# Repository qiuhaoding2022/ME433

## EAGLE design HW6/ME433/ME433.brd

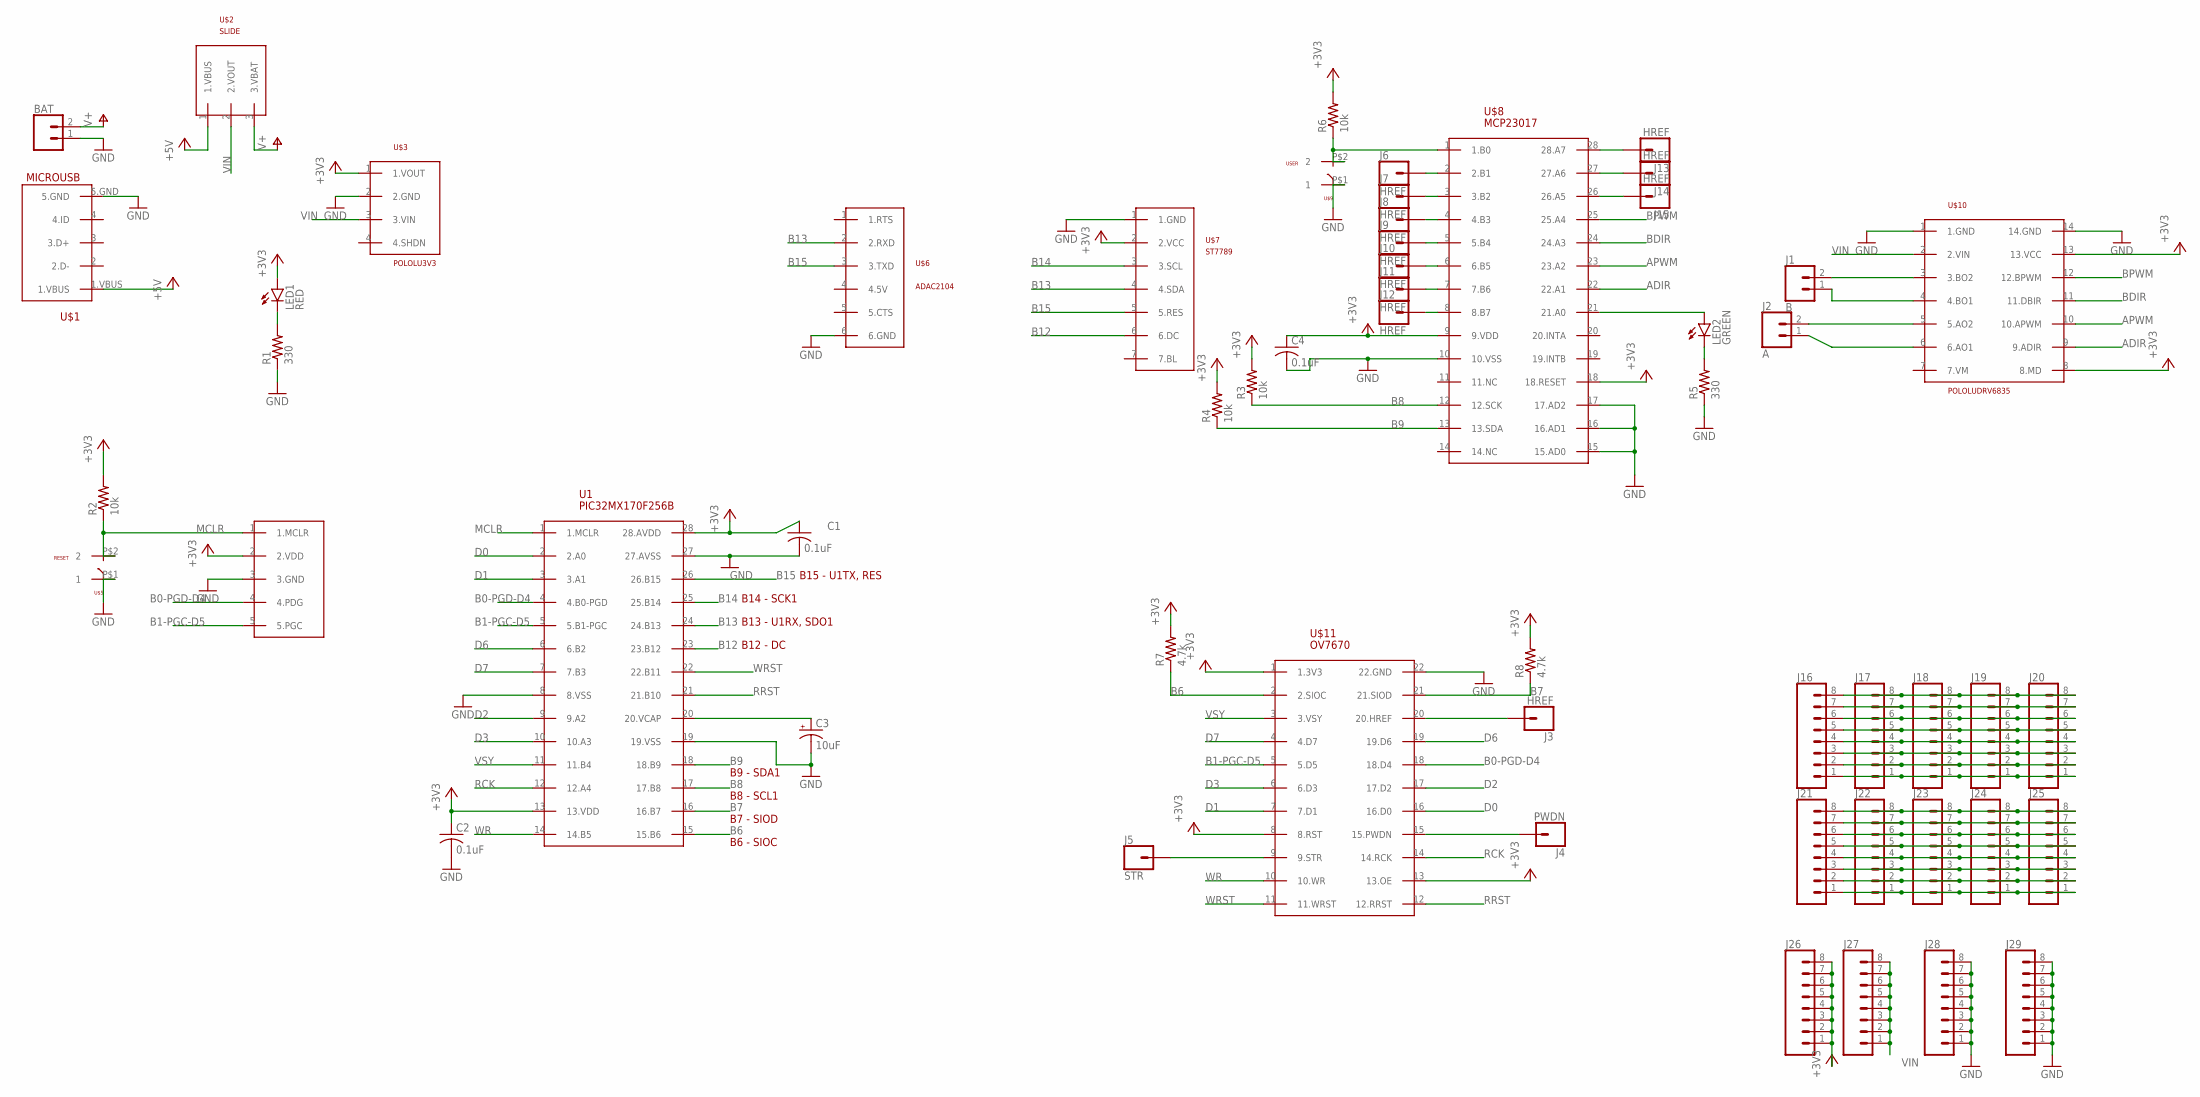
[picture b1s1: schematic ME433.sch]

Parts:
BAT: CONN_02; 1X02
C1, C2, C4: 0.1uF; C025-030X050
C3: 10uF; B45181B
J1: B; 1X02
J2: A; 1X02
J3, J6, J7, J8, J9, J10, J11, J12, J13, J14, J15: HREF; 1X01
J4: PWDN; 1X01
J5: STR; 1X01
J16, J17, J18, J19, J20, J21, J22, J23, J24, J25, J26, J27, J28, J29: CONN_08"; 1X08
LED1: RED; LED3MM
LED2: GREEN; LED3MM
R1, R5: 330; 0207/10
R2, R3, R4, R6: 10k; 0207/10
R7, R8: 4.7k; 0207/10
U1: PIC32MX170F256B; DIL28-3
U$1: MICROUSB
U$2: SLIDE
U$3: POLOLU3V3
U$4: SNAP
U$5: RESET; PUSH
U$6: ADAC2104
U$7: ST7789
U$8: MCP23017; DIL28-3
U$9: USER; PUSH
U$10: POLOLUDRV6835
U$11: OV7670

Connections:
+3V3: C1.1, C2.1, C4.1, J26.1, J26.2, J26.3, J26.4, J26.5, J26.6, J26.7, J26.8, LED1.A, R2.2, R3.2, R4.2, R6.2, R7.2, R8.2, U1.13 (13.VDD), U1.28 (28.AVDD), U$3.1 (1.VOUT), U$4.2 (2.VDD), U$7.2 (2.VCC), U$8.9 (9.VDD), U$8.18 (18.RESET), U$10.8 (8.MD), U$10.13 (13.VCC), U$11.1 (1.3V3), U$11.8 (8.RST), U$11.13 (13.OE)
+5V: U$1.1.VBUS, U$2.1 (1.VBUS)
ADIR: U$8.22 (22.A1), U$10.9 (9.ADIR)
APWM: U$8.23 (23.A2), U$10.10 (10.APWM)
B0-PGD-D4: U1.4 (4.B0-PGD), U$4.4 (4.PDG), U$11.18 (18.D4)
B1-PGC-D5: U1.5 (5.B1-PGC), U$4.5 (5.PGC), U$11.5 (5.D5)
B6: R7.1, U1.15 (15.B6), U$11.2 (2.SIOC)
B7: R8.1, U1.16 (16.B7), U$11.21 (21.SIOD)
B8: R3.1, U1.17 (17.B8), U$8.12 (12.SCK)
B9: R4.1, U1.18 (18.B9), U$8.13 (13.SDA)
B12: U1.23 (23.B12), U$7.6 (6.DC)
B13: U1.24 (24.B13), U$6.2 (2.RXD), U$7.4 (4.SDA)
B14: U1.25 (25.B14), U$7.3 (3.SCL)
B15: U1.26 (26.B15), U$6.3 (3.TXD), U$7.5 (5.RES)
BDIR: U$8.24 (24.A3), U$10.11 (11.DBIR)
BPWM: U$8.25 (25.A4), U$10.12 (12.BPWM)
D0: U1.2 (2.A0), U$11.16 (16.D0)
D1: U1.3 (3.A1), U$11.7 (7.D1)
D2: U1.9 (9.A2), U$11.17 (17.D2)
D3: U1.10 (10.A3), U$11.6 (6.D3)
D6: U1.6 (6.B2), U$11.19 (19.D6)
D7: U1.7 (7.B3), U$11.4 (4.D7)
GND: BAT.1, C1.2, C2.2, C3.-, C4.2, J28.1, J28.2, J28.3, J28.4, J28.5, J28.6, J28.7, J28.8, J29.1, J29.2, J29.3, J29.4, J29.5, J29.6, J29.7, J29.8, R1.1, R5.1, U1.8 (8.VSS), U1.19 (19.VSS), U1.27 (27.AVSS), U$1.5.GND, U$3.2 (2.GND), U$4.3 (3.GND), U$5.P$1 (1), U$6.6 (6.GND), U$7.1 (1.GND), U$8.10 (10.VSS), U$8.15 (15.AD0), U$8.16 (16.AD1), U$8.17 (17.AD2), U$9.P$1 (1), U$10.1 (1.GND), U$10.14 (14.GND), U$11.22 (22.GND)
MCLR: R2.1, U1.1 (1.MCLR), U$4.1 (1.MCLR), U$5.P$2 (2)
unnamed: LED1.K (C), R1.2
unnamed: C3.+, U1.20 (20.VCAP)
unnamed: LED2.K (C), R5.2
unnamed: J1.2, U$10.3 (3.BO2)
unnamed: J1.1, U$10.4 (4.BO1)
unnamed: LED2.A, U$8.21 (21.A0)
unnamed: R6.1, U$8.1 (1.B0), U$9.P$2 (2)
unnamed: J2.2, U$10.5 (5.AO2)
unnamed: J2.1, U$10.6 (6.AO1)
unnamed: J5.1, U$11.9 (9.STR)
unnamed: J4.1, U$11.15 (15.PWDN)
unnamed: J3.1, U$11.20 (20.HREF)
unnamed: J6.1, U$8.2 (2.B1)
unnamed: J7.1, U$8.3 (3.B2)
unnamed: J8.1, U$8.4 (4.B3)
unnamed: J9.1, U$8.5 (5.B4)
unnamed: J10.1, U$8.6 (6.B5)
unnamed: J11.1, U$8.7 (7.B6)
unnamed: J12.1, U$8.8 (8.B7)
unnamed: J13.1, U$8.28 (28.A7)
unnamed: J14.1, U$8.27 (27.A6)
unnamed: J15.1, U$8.26 (26.A5)
unnamed: J16.8, J17.8, J18.8, J19.8, J20.8
unnamed: J16.7, J17.7, J18.7, J19.7, J20.7
unnamed: J16.6, J17.6, J18.6, J19.6, J20.6
unnamed: J16.5, J17.5, J18.5, J19.5, J20.5
unnamed: J16.4, J17.4, J18.4, J19.4, J20.4
unnamed: J16.3, J17.3, J18.3, J19.3, J20.3
unnamed: J16.2, J17.2, J18.2, J19.2, J20.2
unnamed: J16.1, J17.1, J18.1, J19.1, J20.1
unnamed: J21.8, J22.8, J23.8, J24.8, J25.8
unnamed: J21.7, J22.7, J23.7, J24.7, J25.7
unnamed: J21.6, J22.6, J23.6, J24.6, J25.6
unnamed: J21.5, J22.5, J23.5, J24.5, J25.5
unnamed: J21.4, J22.4, J23.4, J24.4, J25.4
unnamed: J21.3, J22.3, J23.3, J24.3, J25.3
unnamed: J21.2, J22.2, J23.2, J24.2, J25.2
unnamed: J21.1, J22.1, J23.1, J24.1, J25.1
RCK: U1.12 (12.A4), U$11.14 (14.RCK)
RRST: U1.21 (21.B10), U$11.12 (12.RRST)
V+: BAT.2, U$2.3 (3.VBAT)
VIN: J27.1, J27.2, J27.3, J27.4, J27.5, J27.6, J27.7, J27.8, U$2.2 (2.VOUT), U$3.3 (3.VIN), U$10.2 (2.VIN)
VSY: U1.11 (11.B4), U$11.3 (3.VSY)
WR: U1.14 (14.B5), U$11.10 (10.WR)
WRST: U1.22 (22.B11), U$11.11 (11.WRST)

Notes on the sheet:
B15 - U1TX, RES
B13 - U1RX, SDO1
B14 - SCK1
B12 - DC
B9 - SDA1
B8 - SCL1
B7 - SIOD
B6 - SIOC

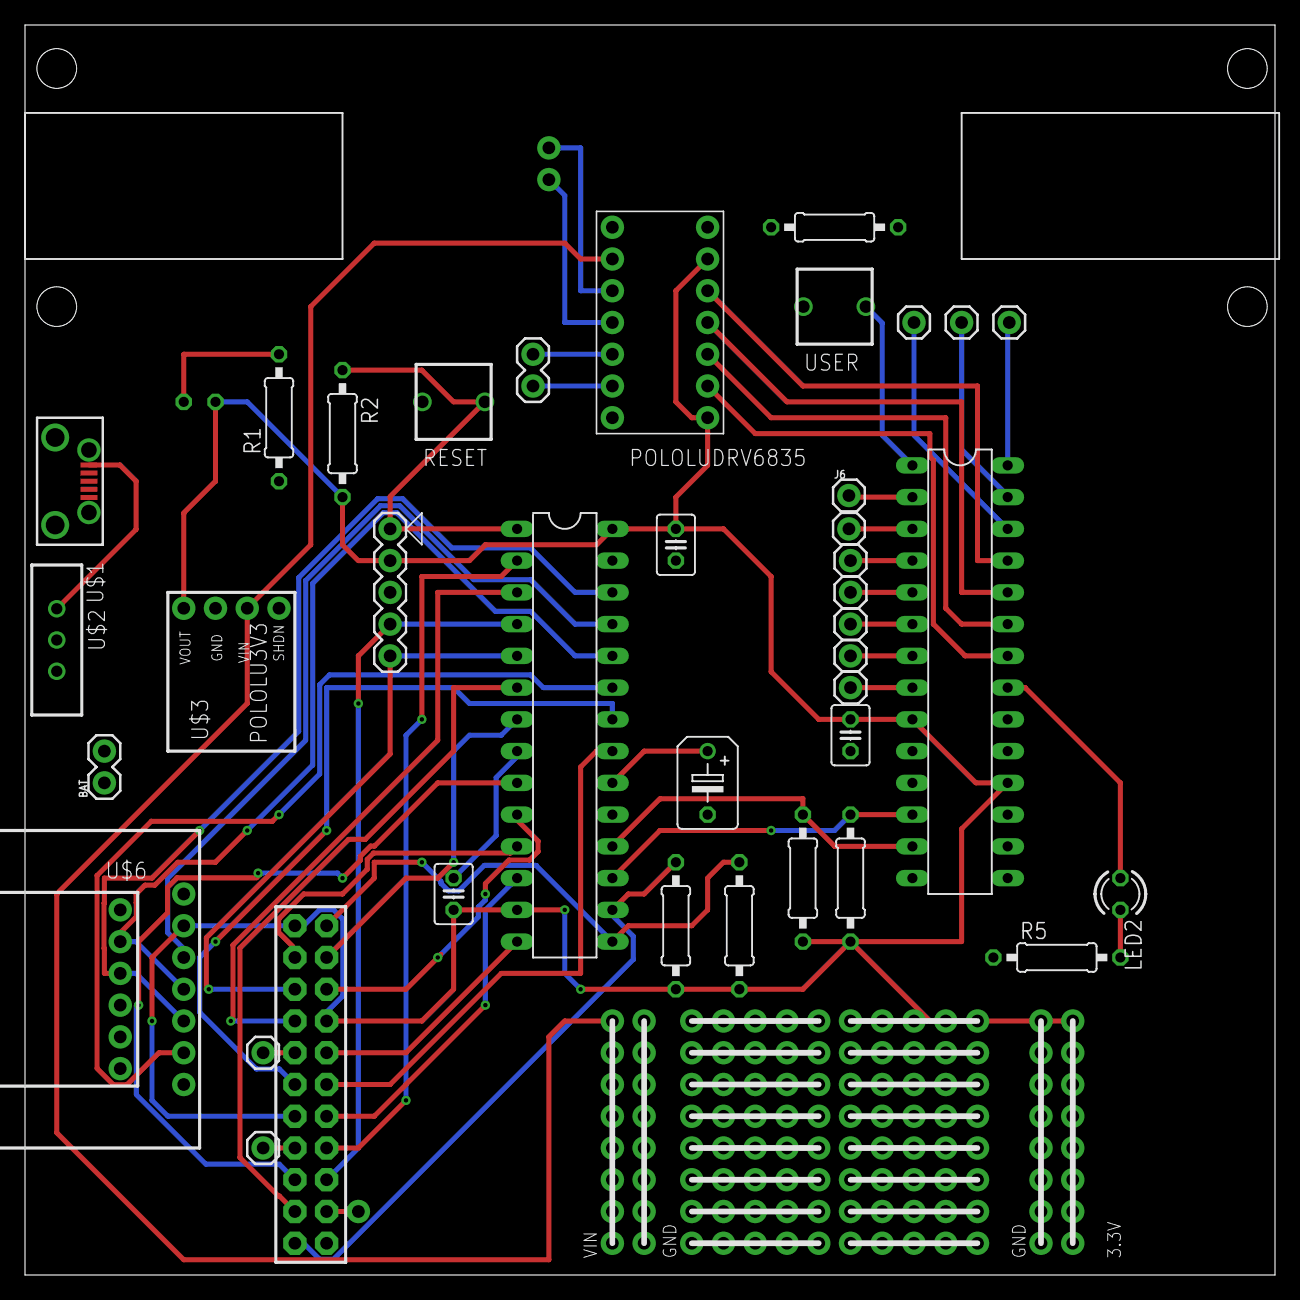
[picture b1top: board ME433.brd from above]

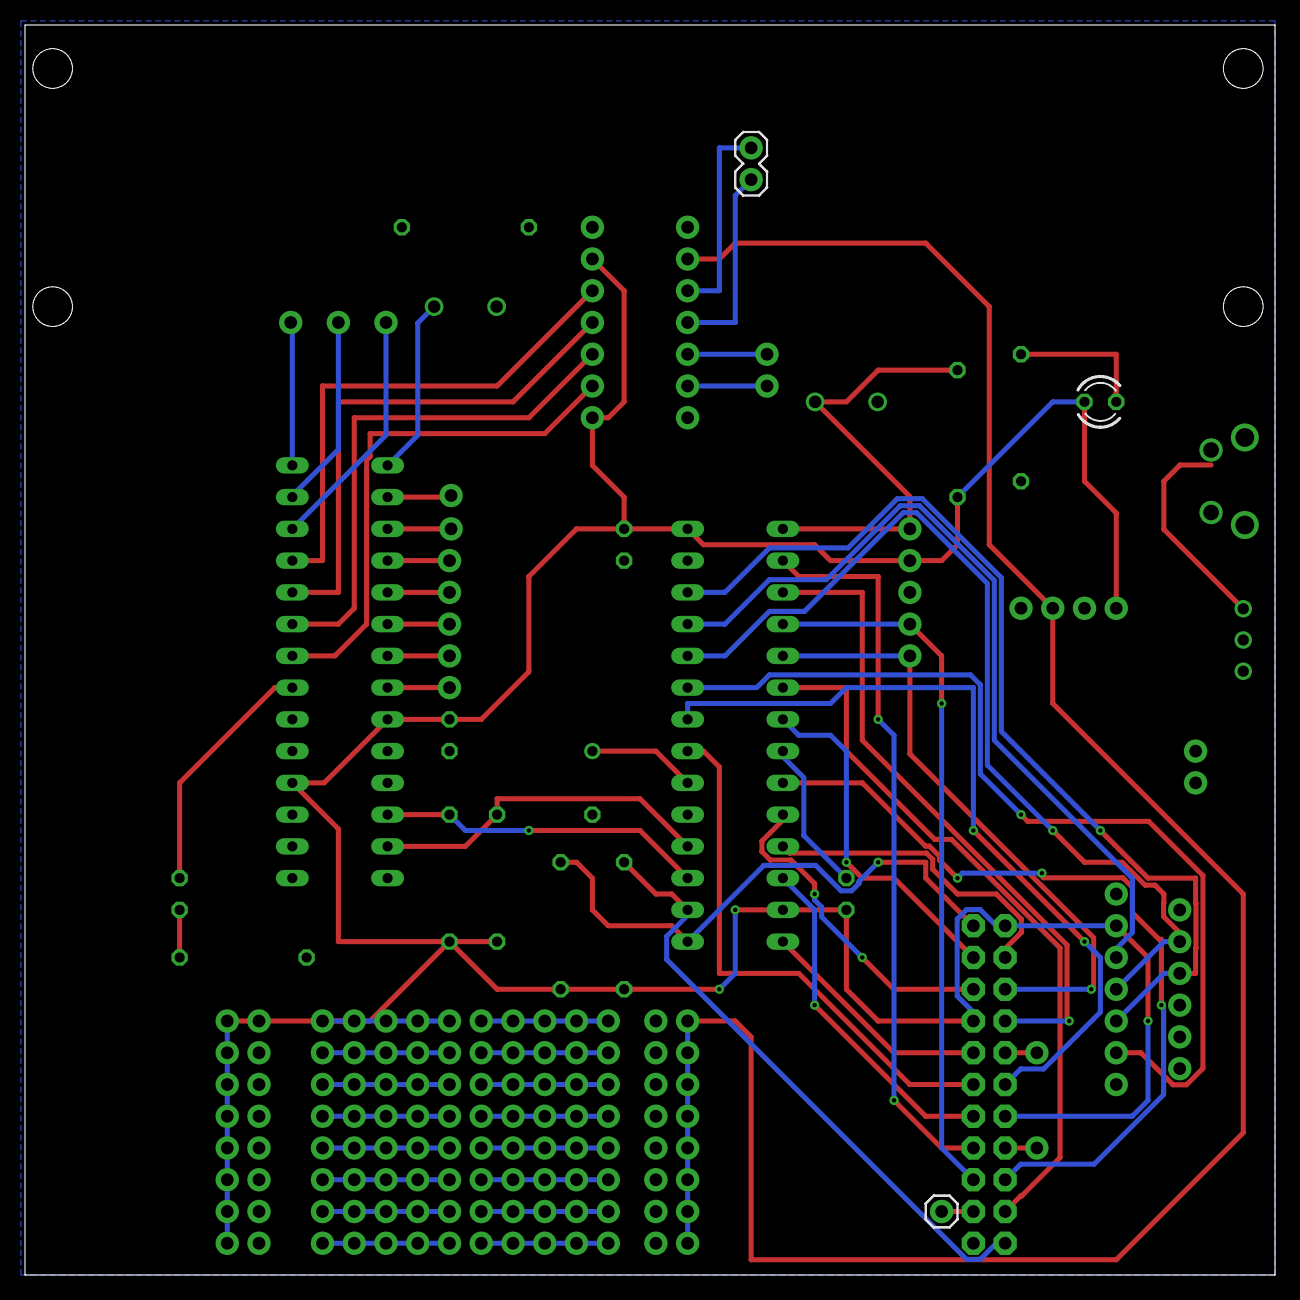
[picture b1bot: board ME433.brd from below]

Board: 2 copper layers, 100.0 x 100.0 mm, 56 parts (3 on the bottom side), 69 nets.

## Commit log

2021-04-06 hw2_q4
    fft plots of four signals
2021-04-06 low-pass filter
    moving average
    python code and plots
2021-04-06 rename folder and add IIR
    IIR filter
    rename Q5 folder to MAF
2021-04-06 FIR upload
    all weights comes from https://fiiir.com/
    Gaussian weighting
2021-04-06 update plot
2021-04-06 plot update
2021-04-06 update plot
    FIR
2021-04-19 Upload HW4 ide project
2021-04-19 upload circuit of HW4
2021-05-01 update LATA and TRIS
    put TRIS and LAT setup outside the while loop
2021-05-01 Create project for hw5
2021-05-01 HW5-UART communication
2021-05-05 HW6 pcb library
2021-05-06 part 1 - library
2021-05-06 schematic
2021-05-17 layout
2021-05-18 HW7 - SPI DAC
2021-05-18 signals update and screenshot
2021-05-30 HW8 i2c
2021-05-30 hw8 i2c test
2021-06-08 hw6 images
2021-06-08 create hw 9 project
2021-06-09 update code
2021-06-09 HW10 _ rainbow led
    WS2812B
2021-06-09 HW 11 - IMU
2021-06-09 HW 14 and other changes
    Motor Control
2021-06-09 new sin trajectory
2021-06-13 HW16 Motor bracket
    image & stl file
2021-06-13 upload demo videos
